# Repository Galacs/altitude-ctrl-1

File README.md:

# Altitude CTRL 1

## Pin definitions

```c
#define I2C_RST_PIN PC13
#define I2C_SDA PB11
#define I2C_SCL PB10

#define STEPPER_STEP PB6
#define STEPPER_DIR PB5
#define STEPPER_EN PB7
#define STEPPER_TX PA2
#define STEPPER_RX PA3

#define CAN_TX_PIN PB9
#define CAN_RX_PIN PB8
#define CAN_STAT_PIN PB12

#define PRESS_SNS_PIN PA7

#define LMS_PIN PB4
#define BTN_PIN PA11
#define BAU_PIN PA15

#define PUMP_PIN PB15
#define RL_1_PIN PB14
#define RL_2_PIN PB13

#define SPI_SCK_PIN PA5
#define SPI_MISO_PIN PA6
#define SPI_CS_PIN PA4
```

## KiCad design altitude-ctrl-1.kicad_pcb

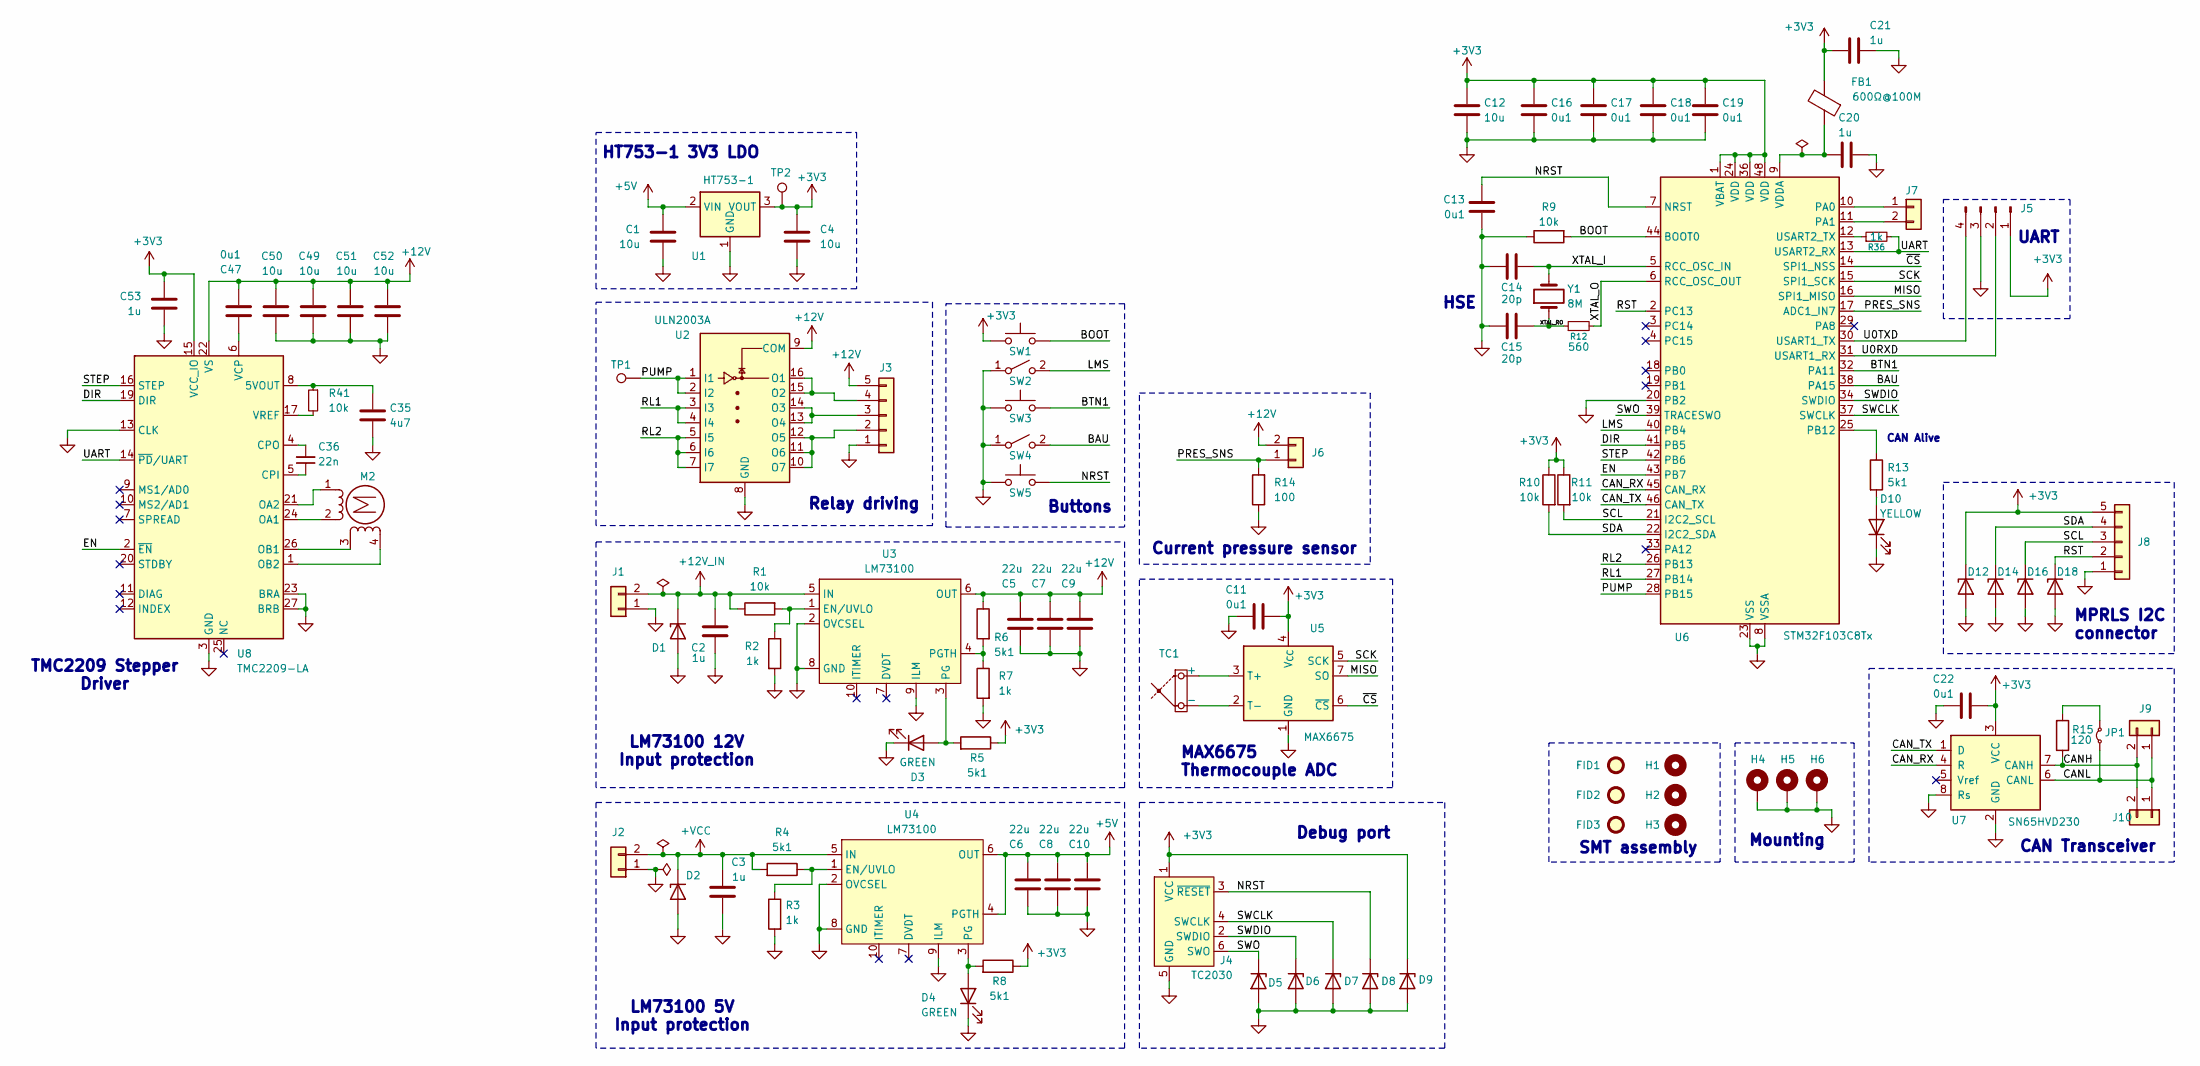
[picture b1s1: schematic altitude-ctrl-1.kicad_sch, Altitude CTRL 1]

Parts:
C1, C4, C12, C49, C50, C51, C52: 10u; C_0805_2012Metric; Manufacturer Part Number GRM21BR61H106KE43L; JLCPCB Part # C440198
C2, C3, C20, C21, C53: 1u; C_0402_1005Metric; Manufacturer Part Number CL05A105KA5NQNC; JLCPCB Part # C52923
C5, C6, C7, C8, C9, C10: 22u; C_0805_2012Metric; Manufacturer Part Number CL21A226MAQNNNE; JLCPCB Part # C45783
C11, C13, C16, C17, C18, C19, C22, C47: 0u1; C_0402_1005Metric; Manufacturer Part Number CL05B104KB54PNC; JLCPCB Part # C307331
C14, C15: 20p; C_0603_1608Metric; Manufacturer Part Number CL10C200JB8NNNC; JLCPCB Part # C1648
C35: 4u7; C_0402_1005Metric; Manufacturer Part Number CL05A475MP5NRNC; JLCPCB Part # C23733
C36: 22n; C_0402_1005Metric; Manufacturer Part Number 0402B223K500NT; JLCPCB Part # C1532
D1, D2: SMAJ12A; D_SMA; Manufacturer Part Number SMAJ12A; JLCPCB Part # C19077531
D3, D4: GREEN; LED_0805_2012Metric; Manufacturer Part Number KT-0805G; JLCPCB Part # C2297
D5, D6, D7, D8, D9, D12, D14, D16, D18: H5VU10U; Diode_DFN1006; Manufacturer Part Number H5VU10U; JLCPCB Part # C22395519
D10: YELLOW; LED_0805_2012Metric; Manufacturer Part Number KT-0805Y; JLCPCB Part # C2296
FB1: 600Ω@100M; L_0805_2012Metric; Manufacturer Part Number MPZ2012S601ATD25; JLCPCB Part # C81034
FID1, FID2, FID3: Fiducial; Fiducial_1mm_Mask2mm
H1, H2, H3: MountingHole; ToolingHole_1.152mm
H4, H5, H6: MountingHole_Pad; MountingHole_3.2mm_M3_Pad_Via
J1, J2, J6: Conn_01x02; TerminalBlock_Phoenix_MKDS-1,5-2-5.08_1x02_P5.08mm_Horizont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
J3, J8: Conn_01x05; TerminalBlock_Phoenix_MKDS-1,5-5-5.08_1x05_P5.08mm_Horizont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
J4: TC2030; Tag-Connect_TC2030-IDC-NL_2x03_P1.27mm_Vertical
J5: Conn_01x04_Pin; PinHeader_1x04_P2.54mm_Vertical
J7: Conn_01x02; PinHeader_1x02_P2.54mm_Vertical
J9, J10: Conn_01x02; JST_XH_B2B-XH-A_1x02_P2.50mm_Vertical
JP1: Jumper_2_Small_Bridged; PinHeader_1x02_P2.54mm_Vertical
M2: Stepper_Motor_bipolar; TerminalBlock_Phoenix_MKDS-1,5-4-5.08_1x04_P5.08mm_Horizont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
R1, R9, R10, R11, R41: 10k; R_0402_1005Metric; Manufacturer Part Number 0402WGF1002TCE; JLCPCB Part # C25744
R2, R3, R7, R36: 1k; R_0402_1005Metric; Manufacturer Part Number 0402WGF1001TCE; JLCPCB Part # C11702
R4, R5, R6, R8, R13: 5k1; R_0402_1005Metric; Manufacturer Part Number 0402WGF5101TCE; JLCPCB Part # C25905
R12: 560; R_0603_1608Metric; Manufacturer Part Number 0603WAF5600T5E; JLCPCB Part # C23204
R14: 100; R_0402_1005Metric; Manufacturer Part Number RT0402BRD07100RL; JLCPCB Part # C705627
R15: 120; R_1206_3216Metric; Manufacturer Part Number 1206W4F1200T5E; JLCPCB Part # C17909
SW1, SW3, SW5: SW_Push; SW_SPST_TS-1088-xR020; Manufacturer Part Number TS-1088-AR02016; JLCPCB Part # C720477
SW2, SW4: SW_SPST; TerminalBlock_Phoenix_MKDS-1,5-2-5.08_1x02_P5.08mm_Horizont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
TC1: Thermocouple_Block; TerminalBlock_Phoenix_MKDS-1,5-2-5.08_1x02_P5.08mm_Horizont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
TP1, TP2: TestPoint; TestPoint_Pad_D2.0mm
U1: HT753-1; SOT-89-3; Manufacturer Part Number HT7533-1; JLCPCB Part # C14289
U2: ULN2003A; SOIC-16_3.9x9.9mm_P1.27mm; Manufacturer Part Number ULN2003ADR; JLCPCB Part # C7512
U3, U4: LM73100; Texas_RPW0010A_VQFN-HR-10_2x2mm_P0.5mm; Manufacturer Part Number LM73100RPWR; JLCPCB Part # C3210761
U5: MAX6675; SOIC-8_3.9x4.9mm_P1.27mm; Manufacturer Part Number C16030; JLCPCB Part # C16030
U6: STM32F103C8Tx; LQFP-48_7x7mm_P0.5mm; Manufacturer Part Number STM32F103C8T6; JLCPCB Part # C8734
U7: SN65HVD230; SOIC-8_3.9x4.9mm_P1.27mm; Manufacturer Part Number SN65HVD230DR; JLCPCB Part # C12084
U8: TMC2209-LA; VQFN-28-1EP_5x5mm_P0.5mm_EP3.7x3.7mm_ThermalVias; Manufacturer Part Number TMC2209-LA-T; JLCPCB Part # C2150710
Y1: 8M; Crystal_SMD_5032-2Pin_5.0x3.2mm; Manufacturer Part Number X50328MSB2GI; JLCPCB Part # C115962

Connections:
+3V3: C4.1, C11.1, C12.1, C16.1, C17.1, C18.1, C19.1, C21.1, C22.1, C53.1, D9.1 (K), D12.1 (K), FB1.2, J4.1 (VCC), J5.1, J8.5, R5.1, R8.1, R10.1, R11.1, SW1.1, TP2.1 (1_1), U1.3 (VOUT), U5.4 (V_{CC}), U6.1 (VBAT), U6.24 (VDD), U6.36 (VDD), U6.48 (VDD), U7.3 (VCC), U8.15 (VCC_IO)
+5V: C1.1, C6.2, C8.2, C10.2, U1.2 (VIN), U4.4 (PGTH), U4.6 (OUT)
+12V: C5.2, C7.2, C9.2, C47.1, C49.1, C50.1, C51.1, C52.1, J3.5, J6.2, R6.1, U2.9 (COM), U3.6 (OUT), U8.22 (VS), U8.28 (VS)
+12V_IN: C2.2, D1.1 (K), J1.2, R1.1, U3.5 (IN)
+VCC: C3.2, D2.1 (K), J2.2, R4.2, U4.5 (IN)
/BAU: SW4.2 (B), U6.38 (PA15)
/BOOT: R9.2, SW1.2, U6.44 (BOOT0)
/BTN1: SW3.2, U6.32 (PA11)
/CANH: J9.2, J10.2, R15.1, U7.7 (CANH)
/CANL: J9.1, J10.1, JP1.1 (A), U7.6 (CANL)
/CAN_RX: U6.45 (CAN_RX), U7.4 (R)
/CAN_TX: U6.46 (CAN_TX), U7.1 (D)
/DIR: U6.41 (PB5), U8.19 (DIR)
/EN: U6.43 (PB7), U8.2 (~EN)
/LMS: SW2.2 (B), U6.40 (PB4)
/MISO: U5.7 (SO), U6.16 (SPI1_MISO)
/NRST: C13.1, D8.1 (K), J4.3 (~RESET), SW5.2, U6.7 (NRST)
/PRES_SNS: J6.1, R14.2, U6.17 (ADC1_IN7)
/PUMP: TP1.1 (1_1), U2.1 (I1), U2.2 (I2), U6.28 (PB15)
/RL1: U2.3 (I3), U2.4 (I4), U6.27 (PB14)
/RL2: U2.5 (I5), U2.6 (I6), U2.7 (I7), U6.26 (PB13)
/RST: D18.1 (K), J8.2, U6.2 (PC13)
/SCK: U5.5 (SCK), U6.15 (SPI1_SCK)
/SCL: D16.1 (K), J8.3, R11.2, U6.21 (I2C2_SCL)
/SDA: D14.1 (K), J8.4, R10.2, U6.22 (I2C2_SDA)
/STEP: U6.42 (PB6), U8.16 (STEP)
/SWCLK: D7.1 (K), J4.4 (SWCLK), U6.37 (SWCLK)
/SWDIO: D6.1 (K), J4.2 (SWDIO), U6.34 (SWDIO)
/SWO: D5.1 (K), J4.6 (SWO), U6.39 (TRACESWO)
/U0RXD: J5.2, U6.31 (USART1_RX)
/U0TXD: J5.4, U6.30 (USART1_TX)
/UART: R36.2, U6.13 (USART2_RX), U8.14 (~PD/UART)
/XTAL_I: C14.1, U6.5 (RCC_OSC_IN), Y1.2
/XTAL_O: R12.2, U6.6 (RCC_OSC_OUT)
/XTAL_RO: C15.1, R12.1, Y1.1
/~CS: U5.6 (~CS), U6.14 (SPI1_NSS)
GND: C1.2, C2.1, C3.1, C4.2, C5.1, C6.1, C7.1, C8.1, C9.1, C10.1, C11.2, C12.2, C13.2, C14.2, C15.2, C16.2, C17.2, C18.2, C19.2, C20.2, C21.2, C22.2, C35.2, C49.2, C50.2, C51.2, C52.2, C53.2, D1.2 (A), D2.2 (A), D3.1 (K), D4.1 (K), D5.2 (A), D6.2 (A), D7.2 (A), D8.2 (A), D9.2 (A), D10.1 (K), D12.2 (A), D14.2 (A), D16.2 (A), D18.2 (A), H4.1 (1_1), H5.1 (1_1), H6.1 (1_1), J1.1, J2.1, J3.1, J4.5 (GND), J5.3, J8.1, R2.2, R3.2, R7.2, R9.1, R14.1, SW2.1 (A), SW3.1, SW4.1 (A), SW5.1, U1.1 (GND), U2.8 (GND), U3.2 (OVCSEL), U3.8 (GND), U3.9 (ILM), U4.2 (OVCSEL), U4.8 (GND), U4.9 (ILM), U5.1 (GND), U6.8 (VSSA), U6.20 (PB2), U6.23 (VSS), U6.35 (VSS), U6.47 (VSS), U7.2 (GND), U7.8 (Rs), U8.3 (GND), U8.13 (CLK), U8.18 (GND), U8.23 (BRA), U8.27 (BRB), U8.29 (GND)
unnamed: D3.2 (A), R5.2, U3.3 (PG)
unnamed: D4.2 (A), R8.2, U4.3 (PG)
unnamed: D10.2 (A), R13.2
unnamed: J3.2, U2.10 (O7), U2.11 (O6), U2.12 (O5)
unnamed: J3.3, U2.13 (O4), U2.14 (O3)
unnamed: J3.4, U2.15 (O2), U2.16 (O1)
unnamed: J7.1, U6.10 (PA0)
unnamed: J7.2, U6.11 (PA1)
unnamed: JP1.2 (B), R15.2
unnamed: M2.1 (-_1), U8.21 (OA2)
unnamed: TC1.1 (+), U5.3 (T+)
unnamed: TC1.2 (-), U5.2 (T-)
unnamed: R1.2, R2.1, U3.1 (EN/UVLO)
unnamed: R6.2, R7.1, U3.4 (PGTH)
unnamed: R3.1, R4.1, U4.1 (EN/UVLO)
unnamed: R36.1, U6.12 (USART2_TX)
unnamed: R13.1, U6.25 (PB12)
unnamed: C20.1, FB1.1, U6.9 (VDDA)
unnamed: C35.1, R41.1, U8.8 (5VOUT)
unnamed: C36.1, U8.5 (CPI)
unnamed: C36.2, U8.4 (CPO)
unnamed: M2.2, U8.24 (OA1)
unnamed: M2.3, U8.26 (OB1)
unnamed: M2.4, U8.1 (OB2)
unnamed: C47.2, U8.6 (VCP)
unnamed: R41.2, U8.17 (VREF)

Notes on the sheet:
MAX6675 Thermocouple ADC
LM73100 5V Input protection
Debug port
Mounting
HT753-1 3V3 LDO
LM73100 12V Input protection
SMT assembly
MPRLS I2C connector
HSE
Relay driving
CAN Alive
Buttons
TMC2209 Stepper Driver
UART
Current pressure sensor
CAN Transceiver

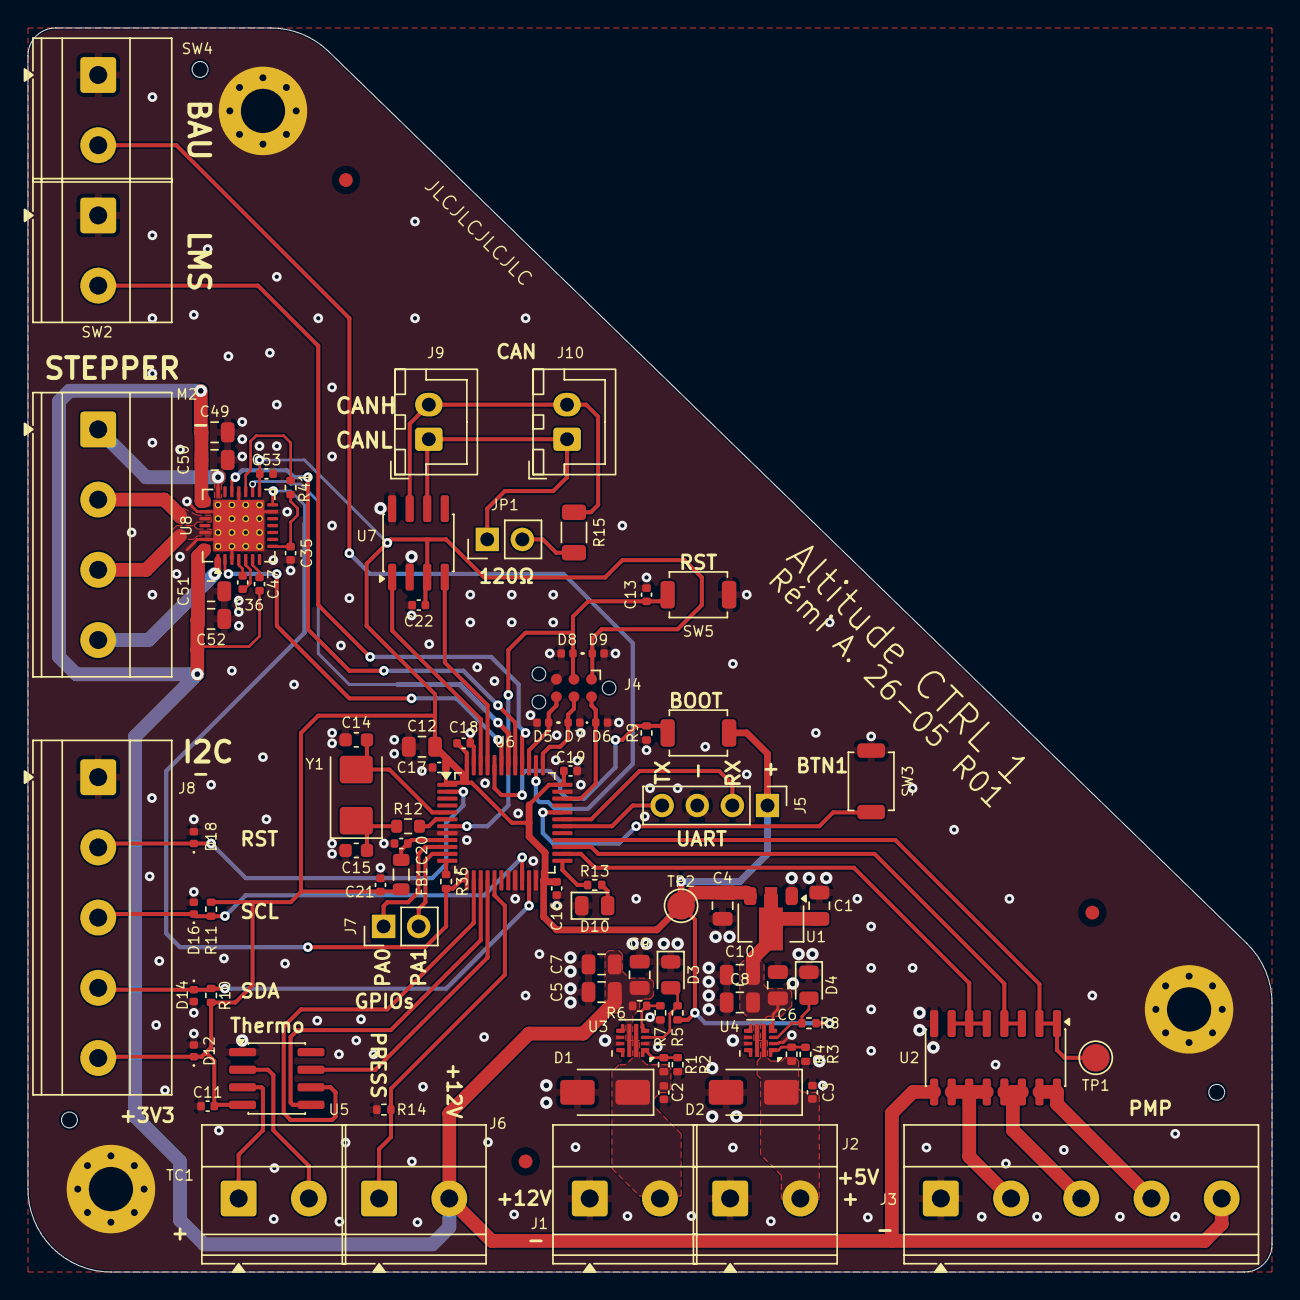
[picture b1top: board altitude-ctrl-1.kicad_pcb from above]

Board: 2 copper layers, 90.0 x 90.0 mm, 100 parts (0 on the bottom side), 63 nets.

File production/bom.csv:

Designator,Footprint,Quantity,Value,LCSC Part #
"C1, C12, C4, C49, C50, C51, C52",0805,7,10u,C440198
"C10, C5, C6, C7, C8, C9",0805,6,22u,C45783
"C11, C13, C16, C17, C18, C19, C22, C47",0402,8,0u1,C307331
"C14, C15",0603,2,20p,C1648
"C2, C20, C21, C3, C53",0402,5,1u,C52923
C35,0402,1,4u7,C23733
C36,0402,1,22n,C1532
"D1, D2",D_SMA,2,SMAJ12A,C19077531
D10,0805,1,YELLOW,C2296
"D12, D14, D16, D18, D5, D6, D7, D8, D9",Diode_DFN1006,9,H5VU10U,C22395519
"D3, D4",0805,2,GREEN,C2297
FB1,0805,1,600Ω@100M,C81034
J7,PinHeader_1x02_P2.54mm_Vertical,1,Conn_01x02,
"R1, R10, R11, R41, R9",0402,5,10k,C25744
R12,0603,1,560,C23204
"R13, R4, R5, R6, R8",0402,5,5k1,C25905
R14,0402,1,100,C705627
R15,1206,1,120,C17909
"R2, R3, R36, R7",0402,4,1k,C11702
"SW1, SW3, SW5",SW_SPST_TS-1088-xR020,3,SW_Push,C720477
U1,SOT-89-3,1,HT753-1,C14289
U2,SOIC-16_3.9x9.9mm_P1.27mm,1,ULN2003A,C7512
"U3, U4",Texas_RPW0010A_VQFN-HR-10_2x2mm_P0.5mm,2,LM73100,C3210761
U5,SOIC-8_3.9x4.9mm_P1.27mm,1,MAX6675,C16030
U6,LQFP-48_7x7mm_P0.5mm,1,STM32F103C8Tx,C8734
U7,SOIC-8_3.9x4.9mm_P1.27mm,1,SN65HVD230,C12084
U8,VQFN-28-1EP_5x5mm_P0.5mm_EP3.7x3.7mm_ThermalVias,1,TMC2209-LA,C2150710
Y1,Crystal_SMD_5032-2Pin_5.0x3.2mm,1,8M,C115962
